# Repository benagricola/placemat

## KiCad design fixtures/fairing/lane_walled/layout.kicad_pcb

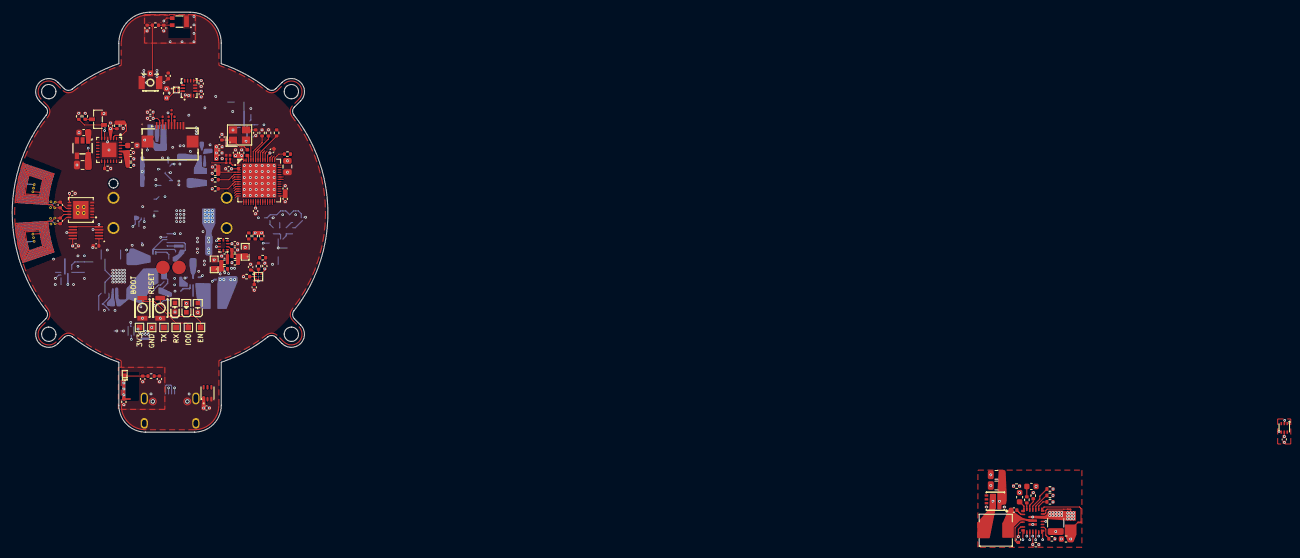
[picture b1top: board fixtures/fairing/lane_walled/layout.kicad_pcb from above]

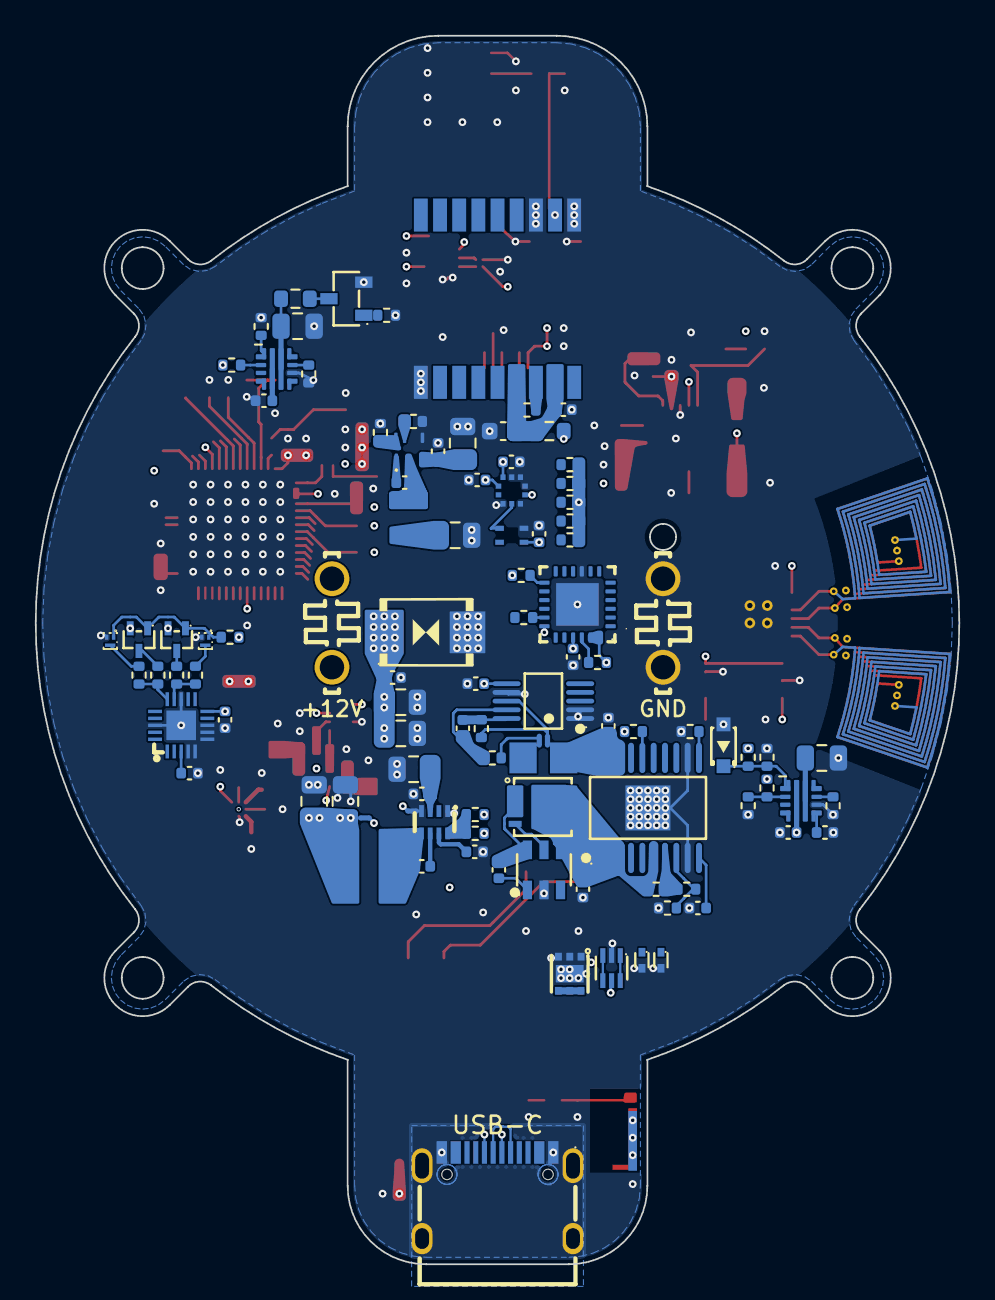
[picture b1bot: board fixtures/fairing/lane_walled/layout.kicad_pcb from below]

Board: 6 copper layers, 53.0 x 70.5 mm, 236 parts (102 on the bottom side), 142 nets.

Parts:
C1, C2, C8, C9, C11, C12, C13, C16, C18, C23, C25, C30, C32, C33, C37, C40, C44, C46, C47, C48, C50, C51, C52, C53, C54, C58, C59, C61, C65, C66, C68, C69, C76, C77, C78, C81, C85: CL05B104KB54PNC; C_0402_1005Metric
C3, C4, C21, C22, C27, C41, C63, C71, C72: GRM21BR61H106KE43L; C_0805_2012Metric
C5, C6, C7: GCM1555C1H1R0JA16D; C_0402_1005Metric
C10, C24, C26, C31, C34, C36, C57: CL05A105KA5NQNC; C_0402_1005Metric
C14, C15: GCM1555C1H100FA16D; C_0402_1005Metric
C17, C75: CL10A106MA8NRNC; C_0603_1608Metric
C19, C20: KAM05CR71A105MH; C_0402_1005Metric
C28, C29: GRM0335C1H1R5CA01D; C_0201_0603Metric
C35, C49, C64, C80: CL05B103KB5NNNC; C_0402_1005Metric
C38, C39: GCM1555C1H160FA16D; C_0402_1005Metric
C42, C43: GRM21BZ71A226ME15L; C_0805_2012Metric
C45: GRM155R71H333KE14D; C_0402_1005Metric
C55, C56, C83, C84: CL05C331JB5NNNC; C_0402_1005Metric
C60: CL10A475KO8NNNC; C_0603_1608Metric
C62: CL10A105KB8NNNC; C_0603_1608Metric
C67: CL10B474KA8NNNC; C_0603_1608Metric
C70: 0603B222K500NT; C_0603_1608Metric
C73: GMK325BJ226MM-T; C_1210_3225Metric
C74: GRM188C81E475ME11D; C_0603_1608Metric
C79, C82: CL21A225KBQNNNE; C_0805_2012Metric
D1: MM3Z5V1ST1G; SOD-323_L1.7-W1.3-LS2.5-RD
FB1: BLM18EG601SN1D; R_0603_1608Metric
J1, J2: YTC1P-3015-01; TESTPOINT-SMD_BD2.3_pitch2.7
L1: LQP03TN2N4B02D; L_0201_0603Metric
L2: LQG15HN2N0C02D; L_0402_1005Metric
L3: MLG1005S24NJT000; L_0402_1005Metric
L4: APH404012C2R2MP01; APH404012_APV_land
L5: PCB sector coil V3; RingCoil_V3_M
L6: PCB sector coil V3; RingCoil_V3
M1: VG1040003D; VG1040003D_outline
NT1, NT2, NT3, NT4, NT5, NT6: NetTie-2_SMD_Pad0.3mm
R1, R24, R25, R29, R40, R41: ERJ-2RKF4701X; R_0402_1005Metric
R2: WR04W2R00FTL; R_0402_1005Metric
R3, R8, R9, R48, R54: ERJ-2GE0R00X; R_0402_1005Metric
R4, R5, R6, R7: RC-01W33R0FT; R_0201_0603Metric
R10, R11, R13, R14, R15, R17, R23, R34, R35, R37, R51, R52, R71, R72: 0402WGF1002TCE; R_0402_1005Metric
R12: ERJ-2RKF1000X; R_0402_1005Metric
R16: 0402WGF5100TCE; R_0402_1005Metric
R18: ERJ-2RKF3162X; R_0402_1005Metric
R19, R21, R45: ERJ-2RKF4702X; R_0402_1005Metric
R20, R22, R36: ERJ-2RKF1001X; R_0402_1005Metric
R26, R32, R38, R39, R42, R46, R49, R50, R55, R59, R60, R61, R62, R65, R68, R69: ERJ-2RKF1003X; R_0402_1005Metric
R27: ERJ-2RKF2003X; R_0402_1005Metric
R28: AC0402FR-071M2L; R_0402_1005Metric
R30, R31: ERJ-2RKF10R0X; R_0402_1005Metric
R33, R56: PE1206DRM470R01L; PE1206_Yageo_Table8
R43, R44, R47, R57, R58: ERJ-2RKF1004X; R_0402_1005Metric
R53: ERJ-2RKF5102X; R_0402_1005Metric
R63: 0402WGF2203TCE; R_0402_1005Metric
R64: ERJ-2RKF6651X; R_0402_1005Metric
R66: 0402WGF4023TCE; R_0402_1005Metric
R67: 0603WAF1001T5E; R_0603_1608Metric
R70: ERJ-2RKF9760X; R_0402_1005Metric
R73: 0402WGF4701TCE; R_0402_1005Metric
R74: 0402WGF1001TCE; R_0402_1005Metric
TH1, TH2: NCU18XH103F60RB; R0603
TP1, TP2, TP3, TP4, TP5, TP6: ?; TestPoint_Pad_1.0x1.0mm
U1: TPS92200D2RXLR; RXL0006A_TI_land
U2: DFE252012F-2R2M=P2; DFE252012F_Murata_land
U3: ANT016008LCS2442MA1; ANT-SMD_6P-L1.6-W0.8-P1.20-1
U4: TMP102AIDRLR(UMW); SOT-563_L1.6-W1.2-P0.50-LS1.6-BL
U5: KT-0603R; LED-SMD_L1.6-W0.8-R-RD
U6: KT-0603W; LED0603-R-RD_WHITE
U7: KT-0603YG; LED0603-RD
U8, U9: B3U-1000P; KEY-SMD_B3U-1000PM
U10: 05A20L10P; FPC-SMD_10P-P0.50_05A20L10P
U11: BMP581; BMP581_Bosch_land
U12: SHT40-AD1B-R3; SHT40_Sensirion_land
U13: W3011; ANT-W3011_DATASHEET
U14: BWU.FL-IPEX1; IPEX-SMD_BWIPX-1-001E
U15: MAX-M10S-00B; GNSS_LCC18_shared_land
U16: DRV2605LDGSR; DGS0010A_TI_land
U17: SMBJ26CA; SMB_L4.6-W3.6-LS5.3-BI
U18, U19: 1217169-1; TH-2P_L7.9-W0.80-P5.08
U20: LTR-303ALS-01; TDFN-6_L2.0-W2.0-P0.65-BL
U21: ESP32-S3FH4R2; QFN-56_L7.0-W7.0-P0.40-BL-EP5.7
U22: S3240000101040; CRYSTAL-SMD_4P-L3_2-W2_5-BL
U23: TPS62933DRLR; SOT-583-8_L2.1-W1.2-P0.50-LS1.6-BR
U24: ADS1115IRUGR; ADS1115_RUG0010A
U25: TPS16630PWPR; HTSSOP-20_L6.5-W4.4-P0.65-LS6.4-TL-EP2.58
U26: INA226AIDGSR; MSOP-10_L3.0-W3.0-P0.50-LS5.0-BL
U27: MDDG06R10Q; DFN-8_L3.3-W3.3-P0.65-BL
U28: LM74700QDBVRQ1; SOT-23-6_L2.9-W1.6-P0.95-LS2.8-TL
U29: LDC1612DNTR; WSON-12_L4_0-W4_0-P0_50-BL-EP
U30: LSM6DS3TR-C; LGA-14_L3.0-W2.5-P0.50-TL
U31: MMC5603NJ; FLIPCHIP-4_L0.8-W0.8-R2-C2-P0.40-TL
U32: TCA9555RTWR; VFQFPN-24_L4.0-W4.0-P0.50-BL-EP2.8
U33: TPS7B6933DBVR; TSOT-23-5_L2.9-W1.6-P0.95-LS2.8-BR
U34: MSPM0L1106TRGER; VQFN-24_L4.0-W4.0-P0.50-TL-EP2.5
U35, U50: 2N7002; SOT-23-3_L2.9-W1.3-P1.90-LS2.4-BR
U36: TYPE-C-31-M-12; TYPE-C-31-M-12-corrected-power-lands
U37: MWSA0518S-2R2MT; IND-SMD_L5.4-W5.2
U38: AON7934; DFN-8_L3.0-W3.0-P0.65-BL_AON7934
U39: TPS55288RPMR; RPM0026A
U40, U41: ESD9B5.0ST5G; SOD-923_L0.8-W0.6-LS1.0-BI
U42: USBLC6-2P6; SOT-666-6_L1.6-W1.2-P0.50-LS1.6-BR
U43: TVS2200DRVR; WSON-6_L2.0-W2.0-P0.65-BL-EP
U44: TPD6S300RUKR; WQFN-20_L3.0-W3.0-P0.40-BL-EP1.7
U45, U46: CSD15380F3; PICOSTAR-3_L0.7-W0.6-P0.35-TL
U47, U48: DMG1013T-7; SC-75-3_L1.6-W0.8-P1.00-LS1.6-BR
U49, U51: TPS259470LRPWR; RPW0010A
U52: RT1715WSC; WLCSP-9_L1.4-W1.4-R3-C3-P0.40-TL

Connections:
ALS_INT: R37.2, U20.5, U32.14
BB_FAULT: R35.2, R49.2, U32.13, U39.14
BL_LEDK: R2.1, U1.6, U10.9
BL_PWM: R1.1, U1.5, U21.10
BOOT_STRAP: R10.2, TP2.1, U8.1, U21.5
DISP_CS: R4.1, U21.17
DISP_DC: R5.1, U21.22
DISP_MOSI: R6.1, U21.21
DISP_RST: U10.4, U21.18
DISP_SCK: R7.1, U21.19
DISP_TE: U10.8, U21.23
EFUSE_SHDN: U25.13, U34.5
EXCITE: R59.2, U21.24, U45.1, U46.1, U47.1, U48.1
GND: C2.2, C3.2, C4.2, C5.2, C6.2, C7.2, C8.2, C9.2, C10.2, C11.2, C12.2, C13.2, C14.2, C15.2, C16.2, C17.2, C18.2, C19.2, C20.2, C21.2, C22.2, C23.2, C24.2, C25.2, C26.2, C27.2, C28.2, C29.2, C30.2, C31.2, C32.2, C33.2, C34.2, C35.2, C36.2, C37.2, C38.2, C39.2, C40.2, C41.2, C42.2, C43.2, C45.2, C46.2, C47.2, C48.2, C49.2, C51.2, C53.2, C54.2, C57.2, C58.2, C59.2, C60.2, C61.2, C62.2, C63.2, C64.2, C65.2, C66.2, C67.2, C71.2, C72.2, C73.2, C74.2, C76.2, C77.2, C78.2, C79.2, C80.2, C81.2, C82.2, C83.2, C84.2, C85.2, D1.2, NT1.1, R1.2, R2.2, R14.2, R15.2, R26.2, R29.2, R42.2, R43.2, R46.2, R48.2, R55.2, R62.2, R64.2, R65.2, R68.2, R69.2, R70.2, R74.2, TH1.2, TH2.2, TP3.1, U1.4, U3.4, U4.2, U4.4, U5.2, U6.2, U8.2, U9.2, U10.10, U10.11, U10.12, U11.3, U11.5, U11.7, U11.8, U11.9, U12.4, U13.2, U14.2, U14.3, U15.1, U15.10, U15.12, U16.4, U16.8, U17.2, U18.1, U18.2, U20.3, U21.57, U22.2, U22.4, U23.1, U23.4, U24.3, U25.9, U25.12, U25.21, U26.1, U26.2, U26.7, U28.2, U29.3, U29.4, U29.6, U29.8, U29.13, U30.1, U30.2, U30.3, U30.6, U30.7, U31.A1, U32.9, U32.25, U33.3, U33.4, U34.4, U34.25, U35.2, U36.1, U36.2, U36.3, U36.4, U36.A1B12, U36.B1A12, U38.5, U38.6, U38.7, U39.9, U39.24, U40.2, U41.2, U42.2, U43.1, U43.2, U43.3, U43.7, U44.4, U44.5, U44.6, U44.7, U44.8, U44.13, U44.18, U44.21, U45.2, U46.2, U49.8, U50.2, U51.8, U52.C2
GNSS_PPS: U15.4, U21.9
GNSS_RX: U15.3, U21.7
GNSS_TX: U15.2, U21.6
IMU_INT1: U21.27, U30.4
INA_ALERT: R34.2, R38.2, U21.16, U26.3, U32.22
LD1: R57.1, R60.2, U21.11, U44.15
LD2: R58.1, R61.2, U21.12, U44.14
LED_BIKE: R23.2, U5.1
LED_STATUS: R12.2, U6.1
LED_USB_K: R36.2, U7.1
LRA_N: J1.1, U16.9
LRA_P: J2.1, U16.7
MCU_EN: C26.1, R11.2, TP4.1, U9.1, U21.4
PD_IRQ: R72.1, U21.47, U52.B2
PGOOD: R32.2, U25.16, U32.12
RAIL_FAULT: R39.2, U25.15, U32.15
REV_EN: R44.2, U28.3, U35.3
RF_50: C6.1, C28.1, L1.2, R3.1
RING_INT: U21.15, U29.5
SCL: R40.2, U11.2, U12.2, U16.2, U20.4, U21.14, U29.1, U30.13, U31.A2, U34.1
SCL_PWR: R24.2, U4.1, U21.37, U24.10, U26.5, U32.19, U39.5, U52.B3
SDA: R41.2, U11.4, U12.1, U16.3, U20.6, U21.13, U29.2, U30.14, U31.B2, U34.24
SDA_PWR: R25.2, U4.6, U21.48, U24.9, U26.4, U32.20, U39.6, U52.C3
UART_RX: TP5.1, U21.50
UART_TX: R16.2, TP6.1
USB_CC1: C83.1, U36.A5, U40.1, U52.C1
USB_CC2: C84.1, U36.B5, U41.1, U52.A1
USB_D_N: U21.25, U36.A7, U36.B7, U42.3, U42.4
USB_D_P: U21.26, U36.A6, U36.B6, U42.1, U42.6
USB_HV: C74.1, C81.1, NT5.1, R56.2, U51.5
USB_SBU1: U36.A8, U44.1
USB_SBU2: U36.B8, U44.2
USB_WET: R71.2, U21.45, U51.2
V3V3: C8.1, C9.1, C10.1, C11.1, C12.1, C13.1, C20.1, C24.1, C25.1, C27.1, C31.1, C32.1, C33.1, C34.1, C35.1, C42.1, C43.1, C46.1, C51.1, C57.1, C58.1, C59.1, C60.1, C61.1, C77.1, C85.1, FB1.1, L2.1, L4.2, NT2.1, R10.1, R11.1, R13.1, R19.1, R21.1, R24.1, R25.1, R32.1, R34.1, R35.1, R37.1, R38.1, R39.1, R40.1, R41.1, R49.1, R59.1, R71.1, R72.2, TP1.1, U4.5, U7.2, U10.2, U11.1, U11.6, U11.10, U12.3, U16.5, U16.6, U16.10, U20.1, U21.20, U21.46, U21.55, U21.56, U24.1, U24.8, U26.6, U29.7, U30.5, U30.8, U30.12, U31.B1, U32.18, U32.21, U32.23, U32.24, U42.5, U44.10, U47.2, U48.2, U52.A3
VBIKE: C21.1, C22.1, C23.1, C52.2, R44.1, R47.1, U17.1, U19.1, U19.2, U27.1, U27.2, U27.3, U28.6
VBUS: C78.1, C82.1, R63.1, R66.1, R67.1, R73.1, U36.A4B9, U36.B4A9, U43.4, U43.5, U43.6, U49.5, U51.6
VBUS_DISCH: R68.1, U21.44, U50.1
VBUS_EN: R55.1, R69.1, U21.36, U39.4, U51.1
VLED: C4.1, U2.2, U10.1
VPROT_IN: C54.1, C62.1, R28.1, U25.1, U25.2, U25.3, U25.6, U27.5, U28.4, U33.1
VSHUNT: C2.1, C3.1, C40.1, C41.1, C71.1, C72.1, C79.1, NT4.1, R23.1, R33.2, U1.3, U23.3, U38.2, U38.3, U38.4, U38.9, U39.3, U49.6
backlight.BL_BOOT: C1.1, U1.1
backlight.SW_BL: C1.2, U1.2, U2.1
ble.ANT24_FEED: C7.1, R3.2, U3.2, U3.3, U3.5, U3.6
ble.ANT24_RAD: C5.1, U3.1
display.DISP_CS_P: R4.2, U10.3
display.DISP_DC_P: R5.2, U10.7
display.DISP_MOSI_P: R6.2, U10.6
display.DISP_SCK_P: R7.2, U10.5
gnss.ANT_FEED: C14.1, R8.1, U14.1, U15.11
gnss.GNSS_VCC: C17.1, C18.1, FB1.2, R9.1, U15.6, U15.8
gnss.GNSS_VCC_RF: C16.1, U15.14
gnss.GNSS_VIO: R9.2, U15.7
gnss.ant_rf.ANT_TRACE: C15.1, R8.2, U13.1
hapticdriver.HAPTIC_REG: C19.1, U16.1
logic.LED_STATUS_DRIVE: R12.1, U21.43
logic.RF_CHIP: C29.1, L1.1, U21.1
logic.STRAP_DOWNLOAD: R15.1, U21.52
logic.STRAP_JTAG: R13.2, U21.8
logic.STRAP_VSPI: R14.1, U21.51
logic.UART_TX_CHIP: R16.1, U21.49
logic.VDD_RF: C30.1, L2.2, U21.2, U21.3
logic.VDD_SPI: C36.1, C37.1, U21.29
logic.XTAL_1: C38.1, L3.2, U22.1
logic.XTAL_N: C39.1, U21.53, U22.3
logic.XTAL_P: L3.1, U21.54
logicsupply.BST_3V3: C44.1, U23.6
logicsupply.FB_3V3: R17.1, R18.2, U23.8
logicsupply.FB_3V3_GND: NT1.2, R17.2
logicsupply.SS_3V3: C45.1, U23.7
logicsupply.SW_3V3: C44.2, L4.1, U23.5
logicsupply.V3V3_SENSE: NT2.2, R18.1
monitoring.ADC_BUCK: C47.1, R20.2, U24.6
monitoring.ADC_PD: C48.1, R22.2, U24.7
monitoring.NTC_BUCK: R19.2, R20.1, TH1.1
monitoring.NTC_PD: R21.2, R22.1, TH2.1
protect.DVDT_SET: C49.1, U25.10
protect.ILIM_SET: R29.1, U25.11
protect.INA_N: C50.2, R30.2, U26.9
protect.INA_P: C50.1, R31.2, U26.10
protect.OVP_SET: R26.1, R27.2, U25.8
protect.REV_CAP: C52.1, U28.1
protect.REV_GATE: U27.4, U28.5
protect.UVLO_SET: R27.1, R28.2, U25.7
protect.VPROT: C53.1, NT3.1, R33.1, U25.18, U25.19, U25.20
protect.VPROT_SENSE: NT3.2, R31.1, U26.8
protect.VSHUNT_SENSE: NT4.2, R30.1
ring.COIL0_A: C55.1, L5.2, U29.9
ring.COIL0_B: C55.2, L5.1, U29.10
ring.COIL1_A: C56.1, L6.1, U29.11
ring.COIL1_B: C56.2, L6.2, U29.12
status.LED_USB_SINK: R36.1, U32.17
supervisor.REV_EN_GATE: R43.1, U34.6, U35.1
supervisor.SUP_BSL: R42.1, U34.14
supervisor.SUP_NRST: C64.1, R45.2, U34.2
supervisor.SUP_VCORE: C67.1, U34.23
supervisor.VIN_SENSE: C65.1, R46.1, R47.2, U34.21
supervisor.V_AON: C63.1, C66.1, R45.1, U33.5, U34.3
usbconverter.AGND: C70.2, C75.2, R48.1, R50.2, R52.2, R53.2, R54.2, U39.7, U39.10
usbconverter.BOOT1: C68.1, U39.22
usbconverter.BOOT2: C69.1, U39.20
usbconverter.CDC_SET: R50.1, U39.16
usbconverter.COMP_BB: R51.1, U39.18
usbconverter.COMP_MID: C70.1, R51.2
usbconverter.DR1H: U38.1, U39.2
usbconverter.DR1L: U38.8, U39.1
usbconverter.FSW_SET: R52.1, U39.8
usbconverter.ILIM_BB: R53.1, U39.17
usbconverter.ISN: NT5.2, U39.13
usbconverter.ISP: NT6.2, U39.12
usbconverter.MODE_BB: R54.1, U39.15
usbconverter.SW1: C68.2, U37.1, U38.10, U39.23
usbconverter.SW2: C69.2, U37.2, U39.21, U39.25
usbconverter.VCC_BB: C75.1, U39.19
usbconverter.VOUT: C73.1, NT6.1, R56.1, U39.11, U39.26
usbpd.moisture.DOWN1: R57.2, U45.3
usbpd.moisture.DOWN2: R58.2, U46.3
usbpd.moisture.PULL1: R60.1, U47.3
usbpd.moisture.PULL2: R61.1, U48.3
usbpd.moisture.SBU_BIAS: C76.1, U44.3
usbpd.sink.SINK_EN: D1.1, R62.1, R63.2, U49.1
usbpd.sink.SINK_LIMIT: R64.1, U49.9
usbpd.sink.SINK_OVLO: R65.1, R66.2, U49.2
usbpd.sink.SINK_SLEW: C80.1, U49.7
usbpd.source.SOURCE_LIMIT: R70.1, U51.9
usbpd.source.VBUS_BLEED: R67.2, U50.3
usbpd.tcpc.TCPC_VBUS: R73.2, U52.A2
usbpd.tcpc.TCPC_VCONN: R74.1, U52.B1

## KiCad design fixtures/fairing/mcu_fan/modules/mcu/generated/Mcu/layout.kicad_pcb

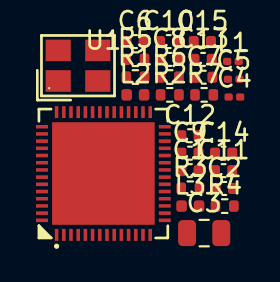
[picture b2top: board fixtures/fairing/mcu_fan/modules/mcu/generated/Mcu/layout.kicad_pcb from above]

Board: 6 copper layers, 27 parts (0 on the bottom side), 16 nets, no tracks yet.

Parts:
C1, C6, C8, C9, C13: CL05B104KB54PNC; C_0402_1005Metric
C2, C7, C10, C12: CL05A105KA5NQNC; C_0402_1005Metric
C3: GRM21BR61H106KE43L; C_0805_2012Metric
C4, C5: GRM0335C1H1R5CA01D; C_0201_0603Metric
C11: CL05B103KB5NNNC; C_0402_1005Metric
C14, C15: GCM1555C1H160FA16D; C_0402_1005Metric
L1: LQP03TN2N4B02D; L_0201_0603Metric
L2: LQG15HN2N0C02D; L_0402_1005Metric
L3: MLG1005S24NJT000; L_0402_1005Metric
R1, R2, R4, R5, R6: 0402WGF1002TCE; R_0402_1005Metric
R3: ERJ-2RKF1000X; R_0402_1005Metric
R7: 0402WGF5100TCE; R_0402_1005Metric
U1: ESP32-S3FH4R2; QFN-56_L7.0-W7.0-P0.40-BL-EP5.7
U2: S3240000101040; CRYSTAL-SMD_4P-L3_2-W2_5-BL

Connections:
BOOT_STRAP: R1.2, U1.5
GND: C1.2, C2.2, C3.2, C4.2, C5.2, C6.2, C7.2, C8.2, C9.2, C10.2, C11.2, C12.2, C13.2, C14.2, C15.2, R5.2, R6.2, U1.57, U2.2, U2.4
LED_STATUS_DRIVE: R3.1, U1.43
MCU_EN: C2.1, R2.2, U1.4
RF_50: C4.1, L1.2
RF_CHIP: C5.1, L1.1, U1.1
STRAP_DOWNLOAD: R6.1, U1.52
STRAP_JTAG: R4.2, U1.8
STRAP_VSPI: R5.1, U1.51
UART_TX_CHIP: R7.1, U1.49
V3V3: C1.1, C3.1, C7.1, C8.1, C9.1, C10.1, C11.1, L2.1, R1.1, R2.1, R4.1, U1.20, U1.46, U1.55, U1.56
VDD_RF: C6.1, L2.2, U1.2, U1.3
VDD_SPI: C12.1, C13.1, U1.29
XTAL_1: C14.1, L3.2, U2.1
XTAL_N: C15.1, U1.53, U2.3
XTAL_P: L3.1, U1.54

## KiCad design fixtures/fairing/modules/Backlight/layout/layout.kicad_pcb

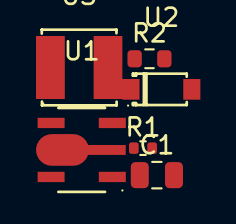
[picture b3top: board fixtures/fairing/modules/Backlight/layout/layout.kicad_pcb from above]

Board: 2 copper layers, 6 parts (0 on the bottom side), 5 nets, no tracks yet.

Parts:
C1: GMC21X5R106M50NT; C_0805_2012Metric
R1: ERJ-2RKF4701X; R_0402_1005Metric
R2: RC0603FR-072R55L; R_0603_1608Metric
U1: PT4115B89E; SOT-89-5_L4.5-W2.5-P1.50-LS4.5-BR
U2: B5819W; SOD-123_L2.8-W1.8-LS3.7-RD
U3: SWPA4030S331MT; IND-SMD_L4.0-W4.0

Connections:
BL_PWM: R1.1, U1.3
GND: C1.2, R1.2, U1.2
SW_BL: U1.1, U2.2, U3.2
VLED: R2.2, U1.4, U2.1
VSHUNT: C1.1, R2.1, U1.5

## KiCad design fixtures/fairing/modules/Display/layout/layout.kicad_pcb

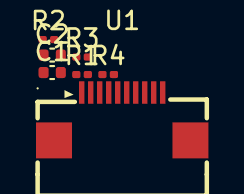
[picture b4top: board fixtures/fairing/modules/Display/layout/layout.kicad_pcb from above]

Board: 2 copper layers, 7 parts (0 on the bottom side), 6 nets, no tracks yet.

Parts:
C1: GCM155R71H104KE02D; C_0402_1005Metric
C2: C0402C105K9PACTU; C_0402_1005Metric
R1, R2, R3, R4: RC0201FR-0733RL; R_0201_0603Metric
U1: 05A20L10P; FPC-SMD_10P-P0.50_05A20L10P

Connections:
DISP_CS_P: R1.2, U1.3
DISP_DC_P: R2.2, U1.7
DISP_MOSI_P: R3.2, U1.6
DISP_SCK_P: R4.2, U1.5
GND: C1.2, C2.2, U1.10, U1.11, U1.12
V3V3: C1.1, C2.1, U1.2

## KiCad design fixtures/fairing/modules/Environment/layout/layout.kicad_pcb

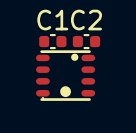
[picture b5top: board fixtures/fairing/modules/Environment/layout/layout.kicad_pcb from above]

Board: 2 copper layers, 3 parts (0 on the bottom side), 2 nets, no tracks yet.

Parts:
C1, C2: GCM155R71H104KE02D; C_0402_1005Metric
U1: BME280; LGA-8_BME280_BL

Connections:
GND: C1.2, C2.2, U1.1, U1.5, U1.7
V3V3: C1.1, C2.1, U1.2, U1.6, U1.8

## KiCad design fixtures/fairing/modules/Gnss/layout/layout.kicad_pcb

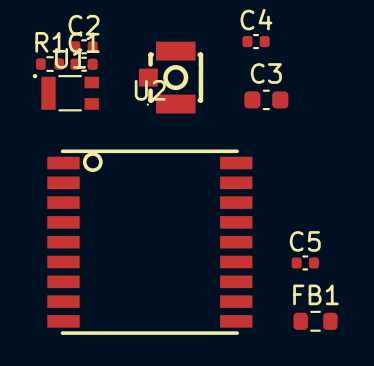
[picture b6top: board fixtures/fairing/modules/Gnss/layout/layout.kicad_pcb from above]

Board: 2 copper layers, 10 parts (0 on the bottom side), 5 nets, no tracks yet.

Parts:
C1, C2: 10pF; C_0402_1005Metric
C3: GRT188R61C106KE13D; C_0603_1608Metric
C4, C5: GCM155R71H104KE02D; C_0402_1005Metric
FB1: BLM18EG601SZ1D; R_0603_1608Metric
R1: ERJ-2GE0R00X; R_0402_1005Metric
U1: W3011; ANT-W3011_DATASHEET
U2: MAX-M10S-00B; SMD-18_L10.1-W9.7-P1.10-TL_SKG09F
U3: BWU.FL-IPEX1; IPEX-SMD_BWIPX-1-001E

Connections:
ANT_FEED: C1.1, R1.1, U2.11, U3.1
GND: C1.2, C2.2, C3.2, C4.2, C5.2, U1.2, U2.1, U2.10, U2.12, U3.2, U3.3
GNSS_VCC: C3.1, C4.1, FB1.2, U2.6, U2.7, U2.8
GNSS_VCC_RF: C5.1, U2.14
ant_rf.ANT_TRACE: C2.1, R1.2, U1.1

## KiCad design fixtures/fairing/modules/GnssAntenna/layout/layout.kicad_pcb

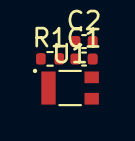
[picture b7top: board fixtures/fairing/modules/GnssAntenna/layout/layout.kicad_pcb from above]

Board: 2 copper layers, 4 parts (0 on the bottom side), 3 nets, no tracks yet.

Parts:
C1, C2: 10pF; C_0402_1005Metric
R1: ERJ-2GE0R00X; R_0402_1005Metric
U1: W3011; ANT-W3011_DATASHEET

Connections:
ANT_FEED: C1.1, R1.1
ANT_TRACE: C2.1, R1.2, U1.1
GND: C1.2, C2.2, U1.2

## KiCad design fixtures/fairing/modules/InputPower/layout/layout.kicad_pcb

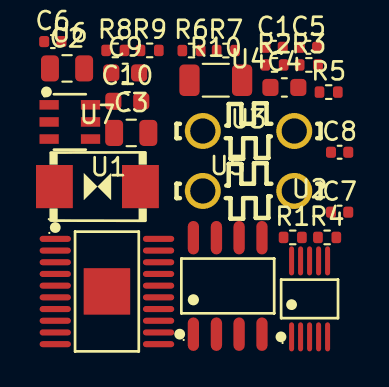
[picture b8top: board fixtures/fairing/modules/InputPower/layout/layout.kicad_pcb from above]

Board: 2 copper layers, 27 parts (0 on the bottom side), 17 nets, no tracks yet.

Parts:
C1: GCM155R71H103KA55D; C_0402_1005Metric
C2, C3: GMC21X5R106M50NT; C_0805_2012Metric
C4, C9, C10: GRM188R72A104KA35D; C_0603_1608Metric
C5, C6, C7, C8: GCM155R71H104KE02D; C_0402_1005Metric
R1, R7: ERJ-2RKF1003X; R_0402_1005Metric
R2: ERJ-2RKF2003X; R_0402_1005Metric
R3: AC0402FR-071M2L; R_0402_1005Metric
R4, R8, R9: ERJ-2RKF4701X; R_0402_1005Metric
R5, R6: ERJ-2RKF10R0X; R_0402_1005Metric
R10: PE1206FKE470R01Z; R_1206_3216Metric
U1: TPS16630PWPR; HTSSOP-20_L6.5-W4.4-P0.65-LS6.4-TL-EP2.58
U2: INA226AIDGSR; MSOP-10_L3.0-W3.0-P0.50-LS5.0-BL
U3, U4: 1217169-1; TH-2P_L7.9-W0.80-P5.08
U5: NCE6005AS; SOP-8_L4.9-W3.9-P1.27-LS6.0-BL
U6: LM74700QDBVTQ1; SOT-23-6_L2.9-W1.6-P0.95-LS2.8-TL
U7: SMBJ30CA; SMB_L4.6-W3.6-LS5.3-BI

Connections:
DVDT_SET: C1.1, U1.10
GND: C1.2, C2.2, C3.2, C4.2, C5.2, C6.2, C7.2, C9.2, C10.2, R1.2, R4.2, U1.9, U1.12, U1.21, U2.1, U2.2, U2.7, U3.1, U3.2, U6.2, U7.2
ILIM_SET: R4.1, U1.11
INA_N: C5.1, R5.2, U2.9
INA_P: C6.1, R6.2, U2.10
OVP_SET: R1.1, R2.2, U1.8
PGOOD: R7.2, U1.16
REV_CAP: C8.1, U6.1
REV_GATE: U5.2, U5.4, U6.5
SCL_PWR: R8.2, U2.5
SDA_PWR: R9.2, U2.4
UVLO_SET: R2.1, R3.2, U1.7
V3V3: C7.1, R7.1, R8.1, R9.1, U2.6
VBIKE: C2.1, C3.1, C4.1, C8.2, U4.1, U4.2, U5.1, U5.3, U6.3, U6.6, U7.1
VPROT: C9.1, R6.1, R10.1, U1.18, U1.19, U1.20, U2.8
VPROT_IN: C10.1, R3.1, U1.1, U1.2, U1.3, U1.6, U5.5, U5.6, U5.7, U5.8, U6.4
VSHUNT: R5.1, R10.2
